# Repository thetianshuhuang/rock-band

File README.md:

# EE319K Final Project: Rock Band
Tianshu Huang and Quinn Buoy

## Game Overview
### Features
- 44.1kHz, 8 bit audio
- Audio and tracks via SD read
- inifinitely many songs supported, just by expanding the menu
- Full resolution (128x160) splash screens

### Dependencies
- tm4c123gh6p.h (tm4c hardware register definition file)
- PLL.h (TM4C PLL; used for 80mHz clock)
- FATFS; ST7735.h and diskio.h from Valvanoware (modified)

### Libraries and Modules
- Network: token network implementation, modified from Serial Token Ring
- Audio: SD read and DAC out; 8 bit x 44.1kHz (44.1kBps bitrate)
- Controller: Four digital and one analog, and derivative routines for the strummer
- Game: Core game control
- Display: SD drivers and display routines
- Menu: Generalized menu library using function pointers
- Graphics: Display routines for the guitar, splash screen, and misc utilities

### File Types
- Packed Image (.pi): packed 5-6-5 GBR 16-bit image, uncompressed, scanning starting from bottom left, across, then up
- Byte wave file (.bw): raw audio file, bit-depth of 8, 44.1kHz
- Rock Band Track (.rb): 16-bit array.
```
| R | Y | B | G | Reserved | Reserved | -- (10) Tick -- |
```
	- R, Y, B, G indicates whether each drum should be hit (1) at that note
or not (0).
	- Tick indicates the number of updates (441 updates/s or 100 audio ticks/update)
before the next note.

## Gameplay
Navigate the menus using the four buttons or by hitting the drums.

At first, the Menu screen will have a black background. Navigate to 'select instrument', and choose the desired instrument. Then, the background will change to match the chosen instrument. Then, select 'Enable Full Mode' to disable the 2:30 time limit on song duration if desired.

All but one device should choose 'Join Lobby'. These devices will wait for the main ('Lobby Leader') device to choose a song, and join in.

All devices on the multiplayer "Waiting for Song Selection" screen will join the main device once a song is selected.
After a song is started, notes will scroll down the screen. Play notes by holding down the appropriate buttons and strumming (guitar/bass) or by hitting the drum pads. Hit notes will increase the score; missed notes will decrease the score. Once enough notes are hit, Star Power is enabled, turning the frets yellow and the notes white, and provides a score multiplier. Poor performance increases the difficulty of obtaining Star Power. The duration of Star Power increases on successful note hits, and decreases greatly on missed notes. 

## Setup instructions

1. Format the SD card as FAT32.

2. Copy the contents of 'resources' to the SD card.

3. Flash code to the TM4C.

4. Plug the TM4C and ST7735R into the main board and insert the SD card in the ST7735R's SD card slot

5. If playing with a guitar, use the 8 pin cable to connect one of the 8 pin connectors on the side of the main board to the 8 pin slot on the guitar. Ensure that the pin on the upper end of the main board (3.3v) is connected to the pin at the bottom of the guitar. Then, connect the male 6 pin connectors on the strummer board and button board. With both boards facing up, the 6 pin cable should be turned 180 degrees.

6. If playing with the drums, plug the 8 pin cable into the top 8 pin connector, with the 3.3v pin connected to the pin closest to the power LED. Then, plug each piezo sensor into the bottom 8 pin connector, with each piezo connected to two adjacent pins.

7. Connect the USB A port of each main board to the USB Micro B port of the next board. Note that the USB cable should not be plugged into either of the TM4C's USB ports. Connect the last board's USB A port to the USB Micro B port of the first board.

8. Connect a 5v source to one of the launchpads, either through the 5v pin or the TM4C's onboard USB port.

## Materials
### Main Client Board
- Main PCB
- Micro USB to USB A cable
- ST7735R
- Micro SD Card
- Male-to-male cable, 8 pin
### Guitar Controller
- Button board
- Strummer base board
- 6 Pin female to female ribbon cable
### Drum Controller
- Op Amp drum controller board
- 4 Piezo sensors

## PCBs
### Main Board

- 1x Micro USB Breakout
- 1x USB A Port
- 1x 3.5mm Jack
- 1x 10&mu;f Capacitor
- 2x 1x8 Right angle Female Connector
- 1x 1x10 Female Connector
- 3x Switch
- Resistors: 1x 10&Omega;, 1x 1k&Omega;, 3x 3k&Omega;, 1x 5.1k&Omega;, 1x 12k&Omega;, 1x 16k&Omega;, 2x 24k&Omega;, 1x 47.1k&Omega;, 1x 91k&Omega;, 1x 180k&Omega;, 1x 360k&Omega;

### Strummer Board
- 1x 1x6 Right angle male connector
- 1x 1x8 Female header
- 1x Red LED
- 1x 220&Omega; Resistor
- 1x Slide Potentiometer

### Button Board
- 4x Buttons
- 4x 10k&Omega; Resistors

### Drums

- 2x 1x8 Female Header
- 1x 20k (or similar) Cermet Potentiometer
- 1x PC324C Quad Op Amp or Equivalent
- 1x Red LED
- 1x 220&Omega; Resistor
- 4x 1M&Omega; Resistors

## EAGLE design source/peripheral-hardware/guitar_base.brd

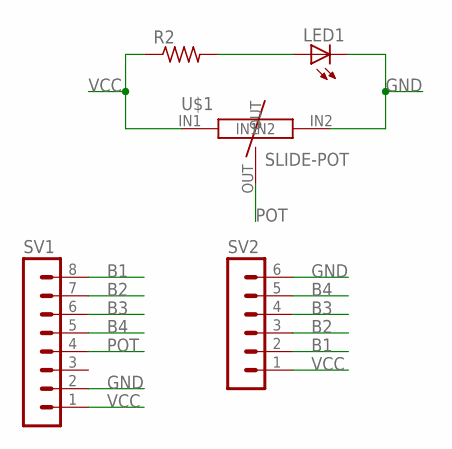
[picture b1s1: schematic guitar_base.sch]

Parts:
LED1: LED5MM
R2: R-US_0207/7; 0207/7
SV1: MA08-1
SV2: MA06-1
U$1: SLIDE-POT

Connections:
B1: SV1.8, SV2.2
B2: SV1.7, SV2.3
B3: SV1.6, SV2.4
B4: SV1.5, SV2.5
GND: LED1.K (C), SV1.2, SV2.6, U$1.IN2
unnamed: LED1.A, R2.2
POT: SV1.4, U$1.OUT
VCC: R2.1, SV1.1, SV2.1, U$1.IN1

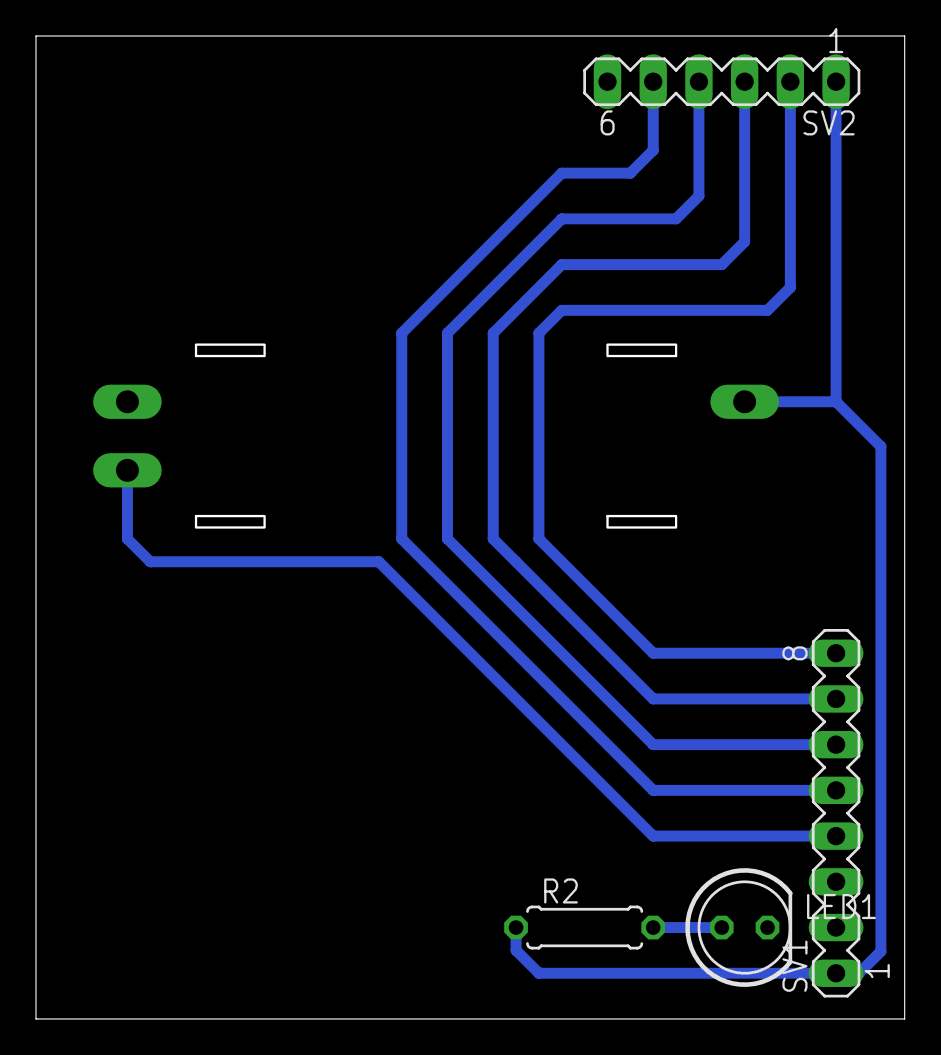
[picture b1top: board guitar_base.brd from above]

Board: 2 copper layers, 48.1 x 54.5 mm, 5 parts (0 on the bottom side), 8 nets.

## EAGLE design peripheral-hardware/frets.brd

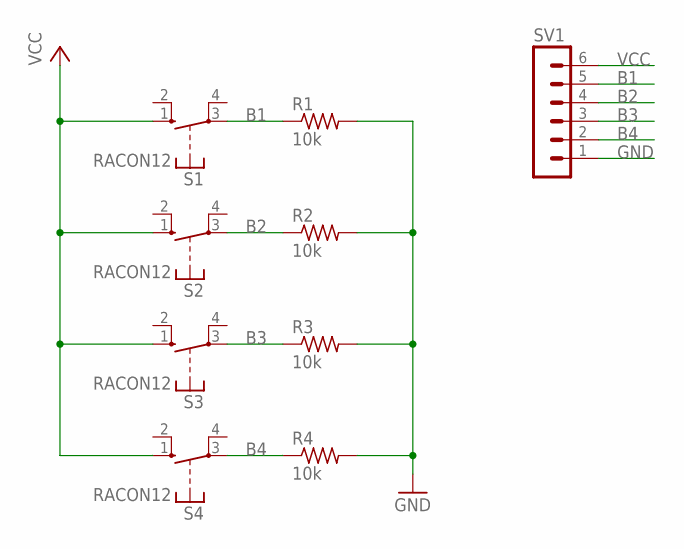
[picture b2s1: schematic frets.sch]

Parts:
R1, R2, R3, R4: 10k; 0207/7
S1, S2, S3, S4: RACON12
SV1: MA06-1

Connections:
B1: R1.1, S1.3, SV1.5
B2: R2.1, S2.3, SV1.4
B3: R3.1, S3.3, SV1.3
B4: R4.1, S4.3, SV1.2
GND: R1.2, R2.2, R3.2, R4.2, SV1.1
VCC: S1.1 (S), S2.1 (S), S3.1 (S), S4.1 (S), SV1.6

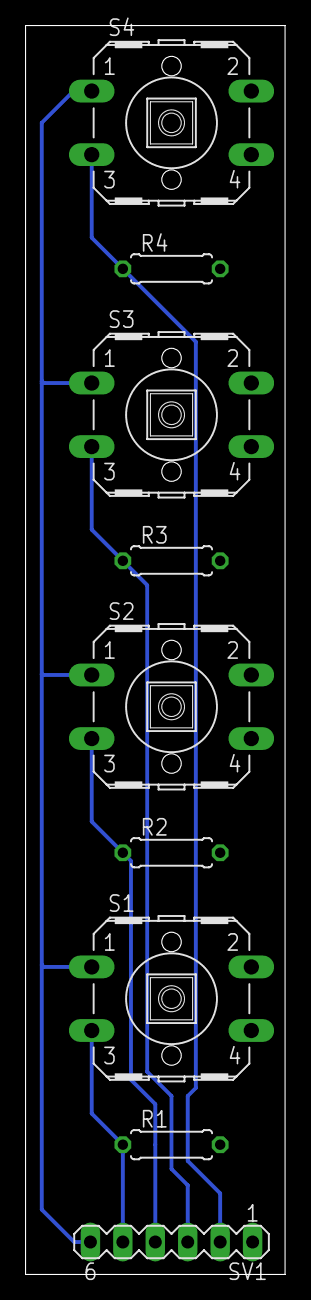
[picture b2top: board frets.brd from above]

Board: 2 copper layers, 20.3 x 97.8 mm, 9 parts (0 on the bottom side), 6 nets.

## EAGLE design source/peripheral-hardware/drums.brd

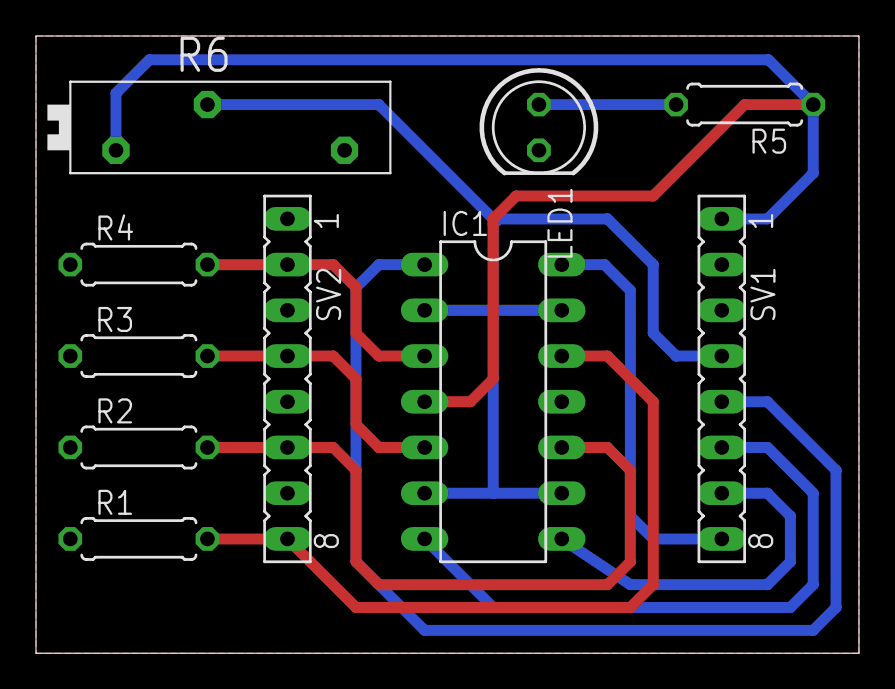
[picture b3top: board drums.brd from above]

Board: 2 copper layers, 45.7 x 34.3 mm, 10 parts (0 on the bottom side), 12 nets.

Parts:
IC1: ICL7641P; DIL14
LED1: LED5MM
R1, R2, R3, R4, R5: 0207/7
R6: PT-SPIN
SV1, SV2: FE08

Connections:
B1: IC1.1, SV1.5
B2: IC1.7, SV1.6
B3: IC1.8, SV1.7
B4: IC1.14, SV1.8
D1: IC1.3, R4.2, SV2.2
D2: IC1.5, R3.2, SV2.4
D3: IC1.10, R2.2, SV2.6
D4: IC1.12, R1.2, SV2.8
GND: IC1.11, LED1.K, R1.1, R2.1, R3.1, R4.1, R6.2, SV1.2, SV2.1, SV2.3, SV2.5, SV2.7
unnamed: LED1.A, R5.2
VCC: IC1.4, R5.1, R6.1, SV1.1
VREF: IC1.2, IC1.6, IC1.9, IC1.13, R6.3, SV1.4

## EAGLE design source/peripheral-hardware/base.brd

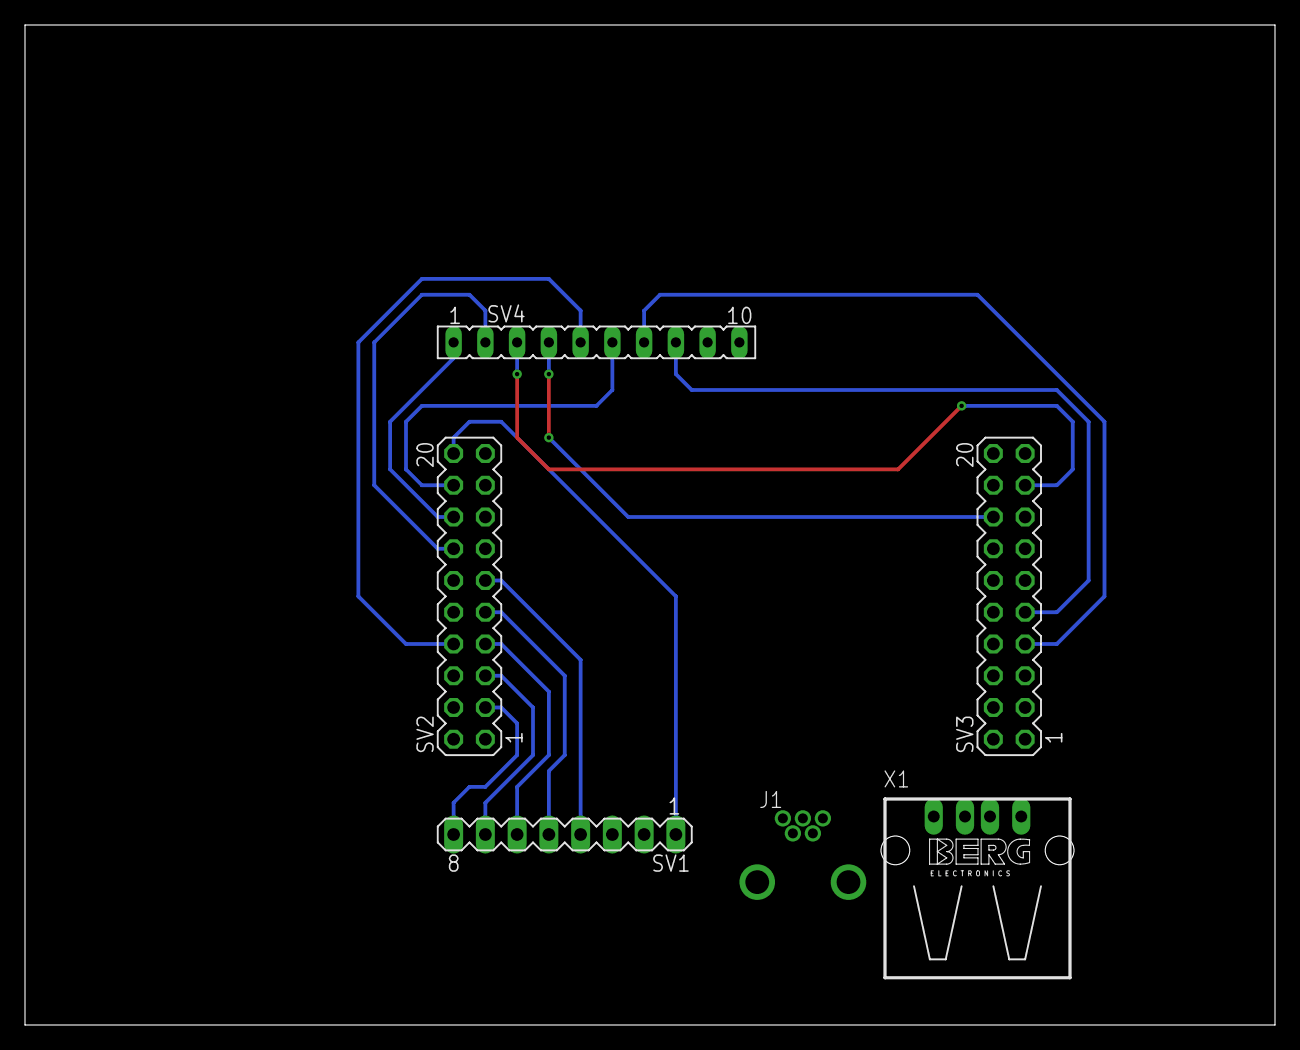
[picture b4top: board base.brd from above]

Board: 2 copper layers, 100.0 x 80.0 mm, 6 parts (0 on the bottom side), 20 nets.

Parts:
J1: USB-MB-H
SV1: MA08-1
SV2, SV3: MA10-2
SV4: FE10
X1: PN87520

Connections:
AIN: SV1.4, SV2.11
D1: SV1.5, SV2.9
D2: SV1.6, SV2.7
D3: SV1.7, SV2.5
D4: SV1.8, SV2.3
DAC0: SV2.16, SV4.1
DAC1: SV2.14, SV4.2
DAC2: SV3.17, SV4.3
DAC3: SV3.16, SV4.4
DAC4: SV2.8, SV4.5
DAC5: SV2.18, SV4.6
DAC6: SV3.7, SV4.7
DAC7: SV3.9, SV4.8
DACOUT: SV4.9, SV4.10
GND: J1.GND, SV1.2, SV2.17, SV3.19, X1.4
RX: SV3.14, X1.2
SN: J1.D-, X1.3
TX: J1.D+, SV3.12
VBUS: J1.VBUS, SV2.19, X1.1
VCC: SV1.1, SV2.20

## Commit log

2018-04-27 Added serial-token-ring submodule
2018-04-27 Added hardware folder
2018-04-27 Added audio test submodule
2018-04-27 Added template
2018-04-28 More core framework
2018-04-28 Added raw audio in variety of forms
2018-04-28 working audio, no sd
2018-04-29 Network driver setup
2018-04-29 controller.h done
2018-04-29 More work on networking
2018-04-29 sd card defs added
2018-04-29 Network forwarding implemented; input bugs related to mispelled register names fixed
2018-04-29 Added thread locking to the network driver
2018-04-29 fixed wrong function definition
2018-04-29 Reorganized, changed thread synchronization to disable interrupts
2018-04-29 almost done with sd
2018-04-29 Started on core game
2018-04-29 Added sd files to uvproj
2018-04-29 fixed gameid
2018-04-29 it compiles but timer5handler might break
2018-04-29 fixed sdcard cs defs
2018-04-29 fixed file close
2018-04-29 sd still breaking
2018-04-29 fixed adc init
2018-04-29 fixed port D init
2018-04-29 Added menus
2018-04-29 something still broken
2018-04-30 Bugfixes
2018-04-30 Rewrote audio driver
2018-04-30 Pushed uvproj
2018-04-30 defined divider
2018-04-30 more audio period fixes
2018-04-30 new short
2018-04-30 new audio
2018-04-30 audio
2018-04-30 11025 audio
2018-04-30 Debug attempt
2018-04-30 small push
2018-04-30 somewhat working audio
2018-04-30 One thing i missed in the previous merge
2018-04-30 Fixed encoding; audio fully working
2018-04-30 Fixed bug in ST7735.c where SetTextColor was ignored by OutChar
2018-04-30 Cosmetic changes in menu.c
2018-04-30 Rencoded songs to fix truncation and overflow (mostly)
2018-04-30 Added another song; small bugfixes to eliminate static-causing errors
2018-05-01 When in doubt, make the buffer bigger
2018-05-01 Working mp3 player + song select
2018-05-01 added guitar pickups
2018-05-01 moved guitar to its own folder
2018-05-01 added more graphics and slanted lines
2018-05-01 fixed line lib
2018-05-01 working base image
2018-05-01 fixes
2018-05-01 Added main menu, started splash screen
2018-05-01 fixed debounce
2018-05-01 Added dsp
2018-05-01 Committed main
2018-05-01 2 buttons work
2018-05-01 Started score
2018-05-01 Revert "Committed main"
    This reverts commit 9c6da3cffdbf126f4f6c31b7696b545273a920fe.
2018-05-01 Revert "Started score"
    This reverts commit fca75ee3bec863c8d9440a3d93ac9168a0821074.
2018-05-01 Revert "2 buttons work"
    This reverts commit d61660353dbaf35d227f04d3ec5020367a01f830.
2018-05-01 Revert "Revert "2 buttons work""
    This reverts commit 26ddff079f539dd616473a53337aec290bd5eee3.
2018-05-01 tien use this
2018-05-01 misc bugfix attempts
2018-05-01 working on note paths onscreen
2018-05-01 finished basic paths for all colors
2018-05-01 Maybe animated notes?
2018-05-01 working notes
2018-05-01 fully animated but bad refresh rate
2018-05-01 Fixed major SD card reading bug
2018-05-01 working perfect animations!!!!
2018-05-01 audio and animation!!!!!!
2018-05-01 minor fixes and increase in resolution
2018-05-01 minor fixes
2018-05-01 Made fifo larger
2018-05-01 minor fix on graphics
2018-05-01 Fixed splash screen
2018-05-01 Fixed uvproj including extra files causing memory error
2018-05-01 Now returns to main menu after song over
2018-05-01 Added score splash screen
2018-05-01 Added song metadata files and new NULL instrument
2018-05-01 Added pause button
2018-05-01 Added instrument select, instrument buffer
2018-05-02 Added framework for score tracking
2018-05-02 Fixed incorrect include
2018-05-02 added multiple note implementaton
2018-05-02 WORKS!!!!!!!!!!!
2018-05-02 WORKS!!!!!!!!!
2018-05-02 created score refresh
2018-05-02 Wrote programmer
2018-05-02 added raw song
2018-05-02 score framework down but not working
2018-05-02 minor fix
2018-05-02 need to debug adc
2018-05-02 Improvements in programmer
2018-05-02 Fixed slide pot
2018-05-02 minor tweaks
2018-05-02 comment
2018-05-02 fixed scorecap
2018-05-02 added sd
2018-05-02 added percent
2018-05-02 Added drums for wild wild life
2018-05-02 Cleaned up code (still need to do guitar.c/h)
2018-05-02 Added file type descriptor
2018-05-03 Changed SD failure mode from delayed update to dropped updates
2018-05-03 Started asynchronous graphics and core game rewrite
2018-05-03 misc bugfixes
2018-05-03 Added star power framework; upped graphics steps from 19 to 32
2018-05-03 Added menu framework, more spash screens
2018-05-03 Added one splash that i forgot
2018-05-04 added music!!!
2018-05-04 Added redraw every 1000 cycles
2018-05-04 added i2c files
2018-05-04 more work on accel defs
2018-05-04 Changes (bugfixes) from last night
2018-05-04 Code cleanup
2018-05-04 Fixed menu bug introduced by refactoring
2018-05-04 working accel?
2018-05-04 breaking for some reason?
2018-05-04 commented out accel
2018-05-04 small fix
2018-05-04 Made demo changes
2018-05-04 Added accel to build
2018-05-16 Untangled dependencies and cleaned up code
2018-05-16 More reorganization
2018-05-16 Reorganized files and added images
2018-05-16 Added some images to README
2018-05-16 Testing image resizing
2018-05-16 Forgot colon
2018-05-16 Testing HTML image encoding instead
2018-05-16 Switched to HTML images
2018-05-16 Put images on the same line
2018-05-16 Added PCB specs to readme
2018-05-16 Misspelled an image name
2018-05-16 Added final image and shuffled order of README
2018-05-19 Fixed spacing of numbering

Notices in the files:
parts and their libraries:
SparkFun-Retired: Licensing: Creative Commons ShareAlike 4.0 International - https://creativecommons.org/licenses/by-sa/4.0
